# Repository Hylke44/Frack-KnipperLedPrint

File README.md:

# Frack-KnipperLedPrint
KnipperLedPrint voor promotie van Frack

Voor meer info zie https://frack.nl/wiki/KnipperLedPrint

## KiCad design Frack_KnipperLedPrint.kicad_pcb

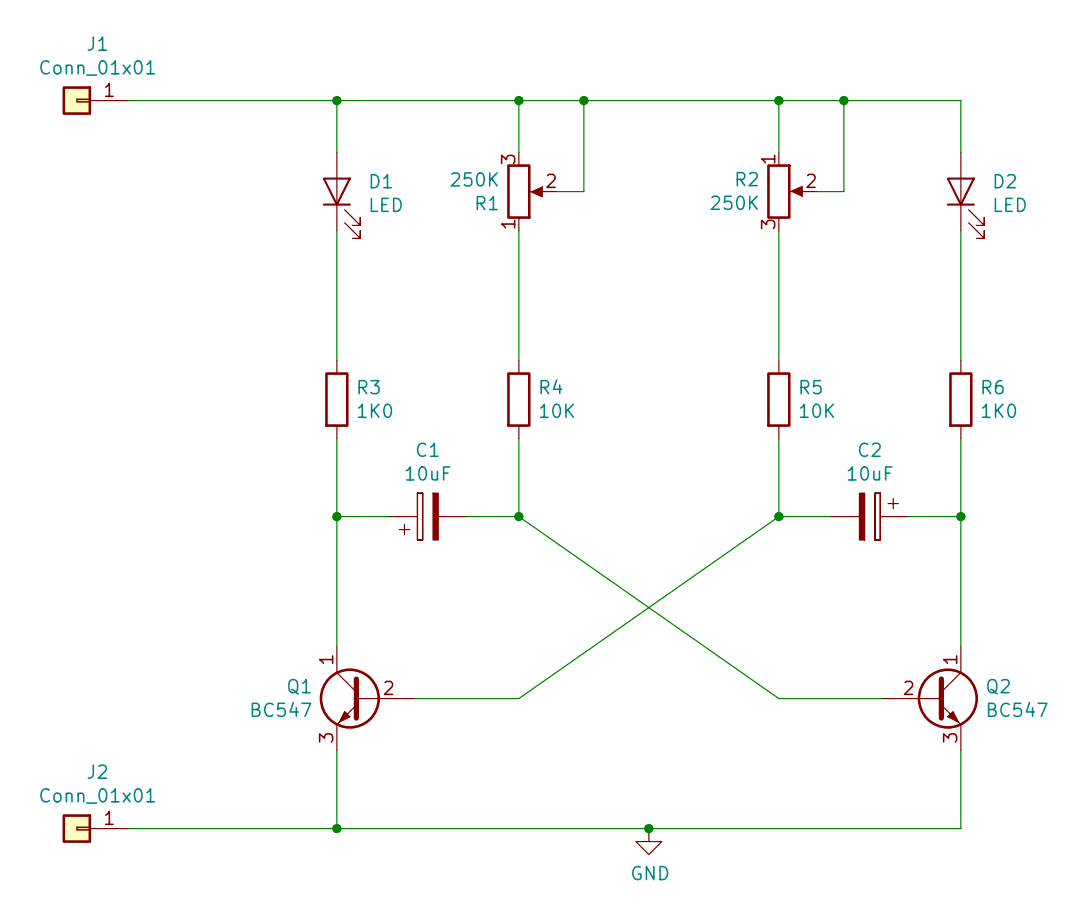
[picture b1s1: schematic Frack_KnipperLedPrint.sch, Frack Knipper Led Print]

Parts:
C1, C2: 10uF; CP_Radial_D5.0mm_P2.50mm
D1, D2: LED; LED_D5.0mm
J1, J2: Conn_01x01; SolderWirePad_1x01_Drill1.2mm
Q1, Q2: BC547; TO-92_HandSolder
R1, R2: 250K; Potentiometer_Piher_PT-6-V_Vertical
R3, R6: 1K0; R_Axial_DIN0207_L6.3mm_D2.5mm_P10.16mm_Horizontal
R4, R5: 10K; R_Axial_DIN0207_L6.3mm_D2.5mm_P10.16mm_Horizontal

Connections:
GND: J2.1, Q1.3 (E), Q2.3 (E)
unnamed: C1.1, Q1.1 (C), R3.2
unnamed: C1.2, Q2.2 (B), R4.2
unnamed: C2.1, Q2.1 (C), R6.2
unnamed: C2.2, Q1.2 (B), R5.2
unnamed: D1.1 (K), R3.1
unnamed: D1.2 (A), D2.2 (A), J1.1, R1.2, R1.3, R2.1, R2.2
unnamed: D2.1 (K), R6.1
unnamed: R1.1, R4.1
unnamed: R2.3, R5.1

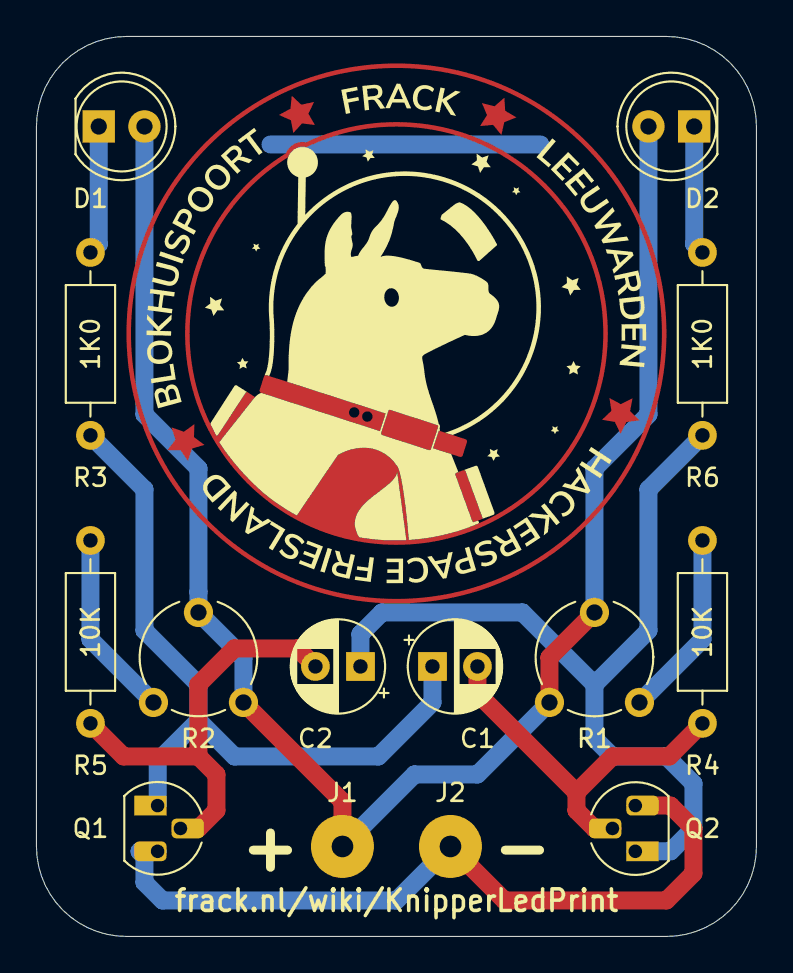
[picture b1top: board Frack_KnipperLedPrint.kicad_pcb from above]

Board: 2 copper layers, 40.0 x 50.0 mm, 14 parts (0 on the bottom side), 10 nets.

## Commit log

2018-11-24 Add files via upload
    Converted old design to Kicad. Added new Frack logo
2018-11-24 Annotations and render
    Changed annotations to match old design
    Added 3d model of potentiometer
    Added render images of pcb
